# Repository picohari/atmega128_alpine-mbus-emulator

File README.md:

# Alpine M-Bus CD Changer Emulator for ATmega128 with LCD and UART

The ALPINE M-BUS is a protocol for the remote control of CD changers used in car audio systems. The purpose of this project is to emulate or pretend the presence of a CD changer to the head-unit to enable the external audio input, tweaking the buttons for other applications or showing data on the display.  

As the audio signal coming from the CD changer is only turned on (un-muted) by the amplifier if the CD changer has replied to the commands coming from the head-unit, it is NOT possible to connect an MP3 player or other auxiliary audio signal from outside the radio without interfacing the M-BUS controller. This is where our project comes into play here: The software decodes the M-BUS commands and emulates the functions of the CD changer/player by sending processed messages (frames) back to the head-unit.

## Features

* All major commands supported: playing, skipping, resuming, disk changing, repeat, scan, etc..  
* M-BUS protocol timings generated/measured by accurate 16bit timer
* Current status and information display on HD44780 LCD
* Debug output on UART/serial console
* Commented & cleaned code, hardware tested on 7525R head-unit
* For own mp3 players or just for fun...

## Installation

Get a local copy of the repository with `git clone https://github.com/picohari/atmega128_alpine-mbus-emulator.git` or simply download the [zip archive](https://github.com/picohari/atmega128_alpine-mbus-emulator/archive/master.zip).

Check your `avr-gcc -v`, it should be similar to mine:
```
Using built-in specs.
COLLECT_GCC=avr-gcc
COLLECT_LTO_WRAPPER=/usr/local/avr/libexec/gcc/avr/4.8.5/lto-wrapper
Target: avr
Configured with: ../configure --target=avr --prefix=/usr/local/avr --disable-nsl
--enable-languages=c,c++ --disable-libssp
Thread model: single
gcc version 4.8.5 (GCC)
```
Compile the code by running the makefile with `make`

On my board the external crystal oscillator has 16Mhz, the timing parameters in the code have been adjusted to match this value. Final tuning was made with logic analyzer.

To program the AVR and set fuses I prefer the [USBasp](http://www.fischl.de/usbasp/).

Run `avrdude -cusbasp -pm128 -Uflash:w:main.hex` to flash the firmware onto the controller.

# Implementation

The code was written for our little friend, the ATmega128 microprocessor from ATMEL and compiled with GCC! The sources for the decoding and encoding routines originates from the well known and ever copied since: http://www.hohensohn.info/mbus/

Some minor changes have been made to the state-machine based communication control routine and to the ISR receiving code, but the software is still in development...

Due to the different voltages between head-unit and the AVR controller, a very small piece of hardware is required to perform level adaptation. With my gear, the original schematic from hohensohn.info didn't work for me, so I took a different level shifting circuit.

## Protocol

The M-BUS is kind of pulse-width modulation: A logical "0" is transmitted as a 0.6ms long pulse and a logical "1" is about 1.8ms

Here we can see the transmission of the PING command on the left side and the reply on the right side. The signals have been already inverted and converted to 5V for the controller pins. M-BUS IN is the signal injected by the AVR to the head-unit. M-BUS OUT is the signal coming from the head-unit.

We read:

|Address  |Command  |Checksum |
| :------:|:-------:|:-------:|
| 0 0 0 1 | 1 0 0 0 | 1 0 1 0 |
|0x01     | 0x08    |0x0A     |

and later the reply (self-decoding on the input line):

|Address  |Command  |Checksum |
| :------:|:-------:|:-------:|
| 1 0 0 1 | 1 0 0 0 | 0 0 1 0 |
|0x09     | 0x08    |0x02     |

Ping - Pong!

## Hardware

The voltage on the M-Bus is about 10V and drops off very quickly if the load is too high. During my tests, the solution with the Z-Diode didn't work, so I took two small signal NPN transistors to do the level shifting:

The signals generated by the microcontroller [OUT] are inverted: a logic "1" (5V) on the output pin pulls down LOW the line on the bus through Q1. A logic "0" will keep it HIGH by the internal pull-up resistor in the head-unit.

If the bus line goes LOW and the beginning of a logic "1" is signalled by the falling edge, R1 pulls the level on the receiving pin [IN] to HIGH and the ISR is triggered.

On the AVR ATmega128 pin PD4 is used as input for receiving packets (Input Capture Pin Timer 1: ICP1) and PD5 is configured as output pin to drive the bus line LOW.

A simple breadboard setup is done in less than 10 minutes. I like very much the ET-BASE boards from ETT (http://www.ett.co.th/product/03000AVR.html) for development and this is how looks like:

## Software

Not much to say, look at the source code. The playing of a CD is emulated by Timer2. Timer1 capture reads the incoming packets and Timer0 is used for sending. I've refactored the original sources and removed this ugly-looking hungarian notation to get some cleaner plain C - it's still not yet completed and leaks further commenting, ...

I will do some more measurements on the timing and include screenshots of the logic analyzer. More to come.

## Contributing

1. Fork it!
2. Create your feature branch: `git checkout -b my-new-feature`
3. Commit your changes: `git commit -am 'Add some feature'`
4. Push to the branch: `git push origin my-new-feature`
5. Submit a pull request :D

## History

TODO: Write history

## Credits

http://www.hohensohn.info/mbus/

https://github.com/kjanesch/pseudochanger

## License

See LICENCE.md file

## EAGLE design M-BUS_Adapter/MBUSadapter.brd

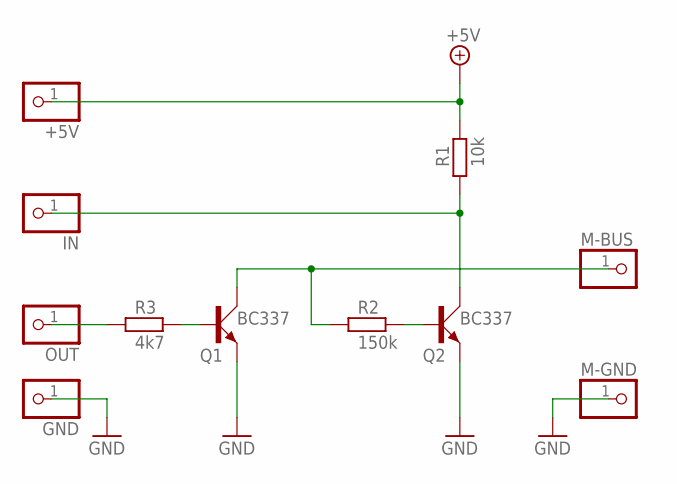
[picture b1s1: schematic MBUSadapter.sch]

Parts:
+5V: PINHD-1X1; 1X01
GND: PINHD-1X1; 1X01
IN: PINHD-1X1; 1X01
M-BUS: PINHD-1X1; 1X01
M-GND: PINHD-1X1; 1X01
OUT: PINHD-1X1; 1X01
Q1, Q2: BC337; SOT54A
R1: 10k; 0207/10
R2: 150k; 0207/10
R3: 4k7; 0207/10

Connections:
+5V: +5V.1, R1.2
GND: GND.1, M-GND.1, Q1.E, Q2.E
unnamed: IN.1, Q2.C, R1.1
unnamed: Q1.B, R3.1
unnamed: OUT.1, R3.2
unnamed: M-BUS.1, Q1.C, R2.1
unnamed: Q2.B, R2.2

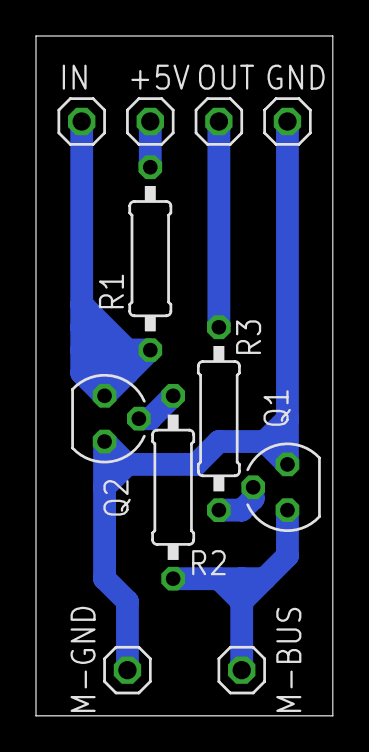
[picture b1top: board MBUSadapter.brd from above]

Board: 2 copper layers, 16.5 x 37.8 mm, 11 parts (0 on the bottom side), 7 nets.

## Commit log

2016-08-23 UART working prototype
2016-08-23 Crashes upon non-hex UART input
2016-08-24 No nested interrupts as presumed...
2016-08-24 UAR HEX Prototype version
2016-08-24 Decoding - missing outfifo for sending
2016-08-26 Working ACK reply - still bad timing somewhere
2016-08-28 Basic reply working - commands not evaluated
2016-08-28 Starting on emulator implementation
2016-08-29 First stable commit
2016-08-29 Corrected missing BCD decoding in LCD
2016-09-02 Added Repeat and Scan flags on LCD
2016-09-02 Added README description
2016-09-03 Added EAGLE sch and brd files
2016-09-03 Images to README file
2016-09-03 Update to README file
2017-01-10 Fixed comments and documentation
2017-01-11 Added pictures for README
2017-01-11 Updated images
2020-10-03 Replaced HD44780 code
2020-10-03 Separated protocol from emulator
2020-10-04 Reworked emulator state machine
2020-10-04 Working on ATmega128
2020-10-04 Code cleanup
2020-10-04 Updated config.h
2020-10-04 Working without LCD time
2020-10-11 New logfile and state machine
2020-10-11 Fixed spaces in logfile
